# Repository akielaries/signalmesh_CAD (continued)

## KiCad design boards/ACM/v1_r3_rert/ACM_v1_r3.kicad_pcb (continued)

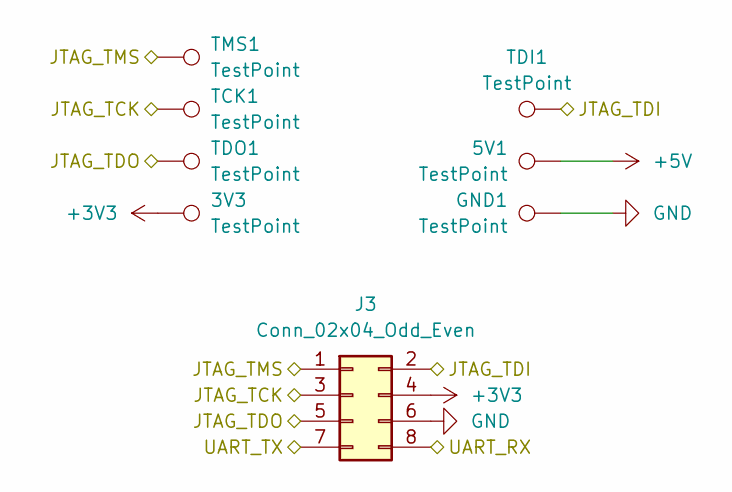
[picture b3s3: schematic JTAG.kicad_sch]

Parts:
3V3, 5V1: TestPoint; TestPoint_Pad_D1.0mm
GND1: TestPoint; TestPoint_Pad_D1.0mm
J3: Conn_02x04_Odd_Even; PinHeader_2x04_P2.54mm_Vertical_SMD
TCK1: TestPoint; TestPoint_Pad_D1.0mm
TDI1: TestPoint; TestPoint_Pad_D1.0mm
TDO1: TestPoint; TestPoint_Pad_D1.0mm
TMS1: TestPoint; TestPoint_Pad_D1.0mm

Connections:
+3V3: 3V3.1 (1_1), J3.4; also elsewhere on the board
+5V: 5V1.1 (1_1); also elsewhere on the board
/A2_JTAG_TDO: J3.5, TDO1.1 (1_1); also elsewhere on the board
/A3_JTAG_TDI: J3.2, TDI1.1 (1_1); also elsewhere on the board
/B1_JTAG_TMS: J3.1, TMS1.1 (1_1); also elsewhere on the board
/B3_IOB56A_FPGA_UART_RX: J3.7; also elsewhere on the board
/C1_JTAG_TCK: J3.3, TCK1.1 (1_1); also elsewhere on the board
/C3_IOB56B_FPGA_UART_TX: J3.8; also elsewhere on the board
GND: GND1.1 (1_1), J3.6; also elsewhere on the board

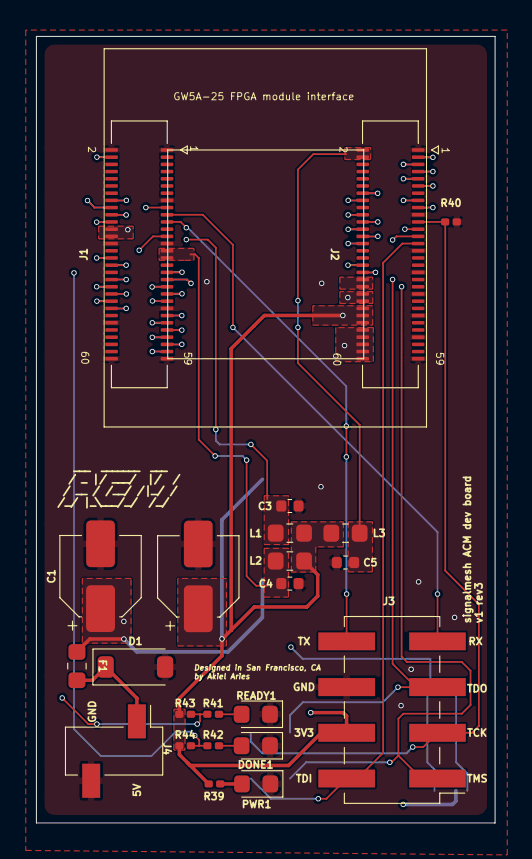
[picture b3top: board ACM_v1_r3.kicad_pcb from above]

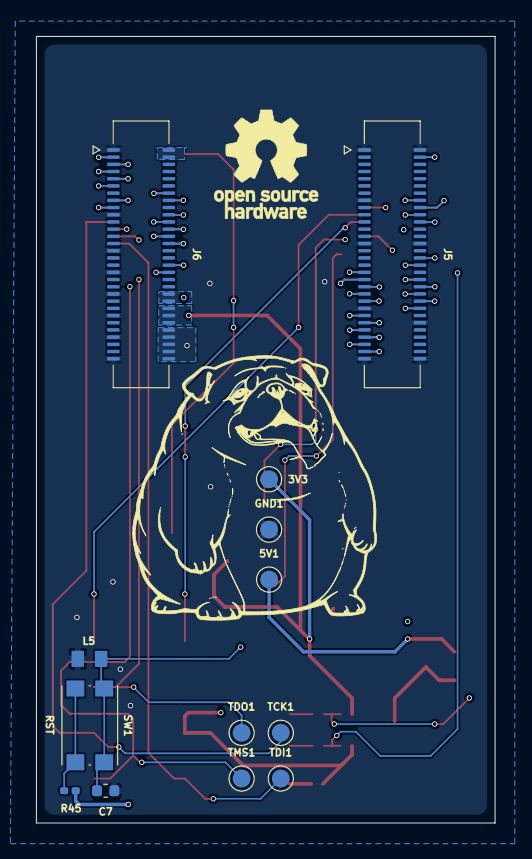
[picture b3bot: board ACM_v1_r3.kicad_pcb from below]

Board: 4 copper layers, 25.5 x 43.7 mm, 36 parts (13 on the bottom side), 66 nets.

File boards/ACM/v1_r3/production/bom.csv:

Designator,Footprint,Quantity,Value,LCSC Part #
"3V3, 5V1, GND1, TCK1, TDI1, TDO1, TMS1",TestPoint_Pad_D1.0mm,7,TestPoint,
"C1, C2",CP_Elec_4x3,2,220uF 10V,
"C3, C4, C5, C7",0402,4,100nF,
D1,D_SOD-123,1,20V 3A,
"DONE1, PWR1, READY1",0603,3,GREEN_LED,
F1,0603,1,6V 2A,
"J1, J2, J5, J6",Hirose_DF40C-60DS-0.4V_2x30_P0.4mm,4,DF40C-60DS-0.4V(51),
J3,PinHeader_2x04_P2.54mm_Vertical_SMD,1,Conn_02x04_Odd_Even,
J4,PinSocket_1x02_P2.54mm_Vertical_SMD_Pin1Left,1,Conn_01x02,
"L1, L2, L3",0603,3,PZ1608D300-3R0TF,
L5,INDC1005X45,1,LXES15AAA1-153,
"R39, R41, R42",0201,3,4.7k,
R40,0201,1,5.1K,
"R43, R44",0201,2,49.9k,
R45,0201,1,100R,
SW1,SW_Push_1P1T_NO_CK_KMR2,1,RST,

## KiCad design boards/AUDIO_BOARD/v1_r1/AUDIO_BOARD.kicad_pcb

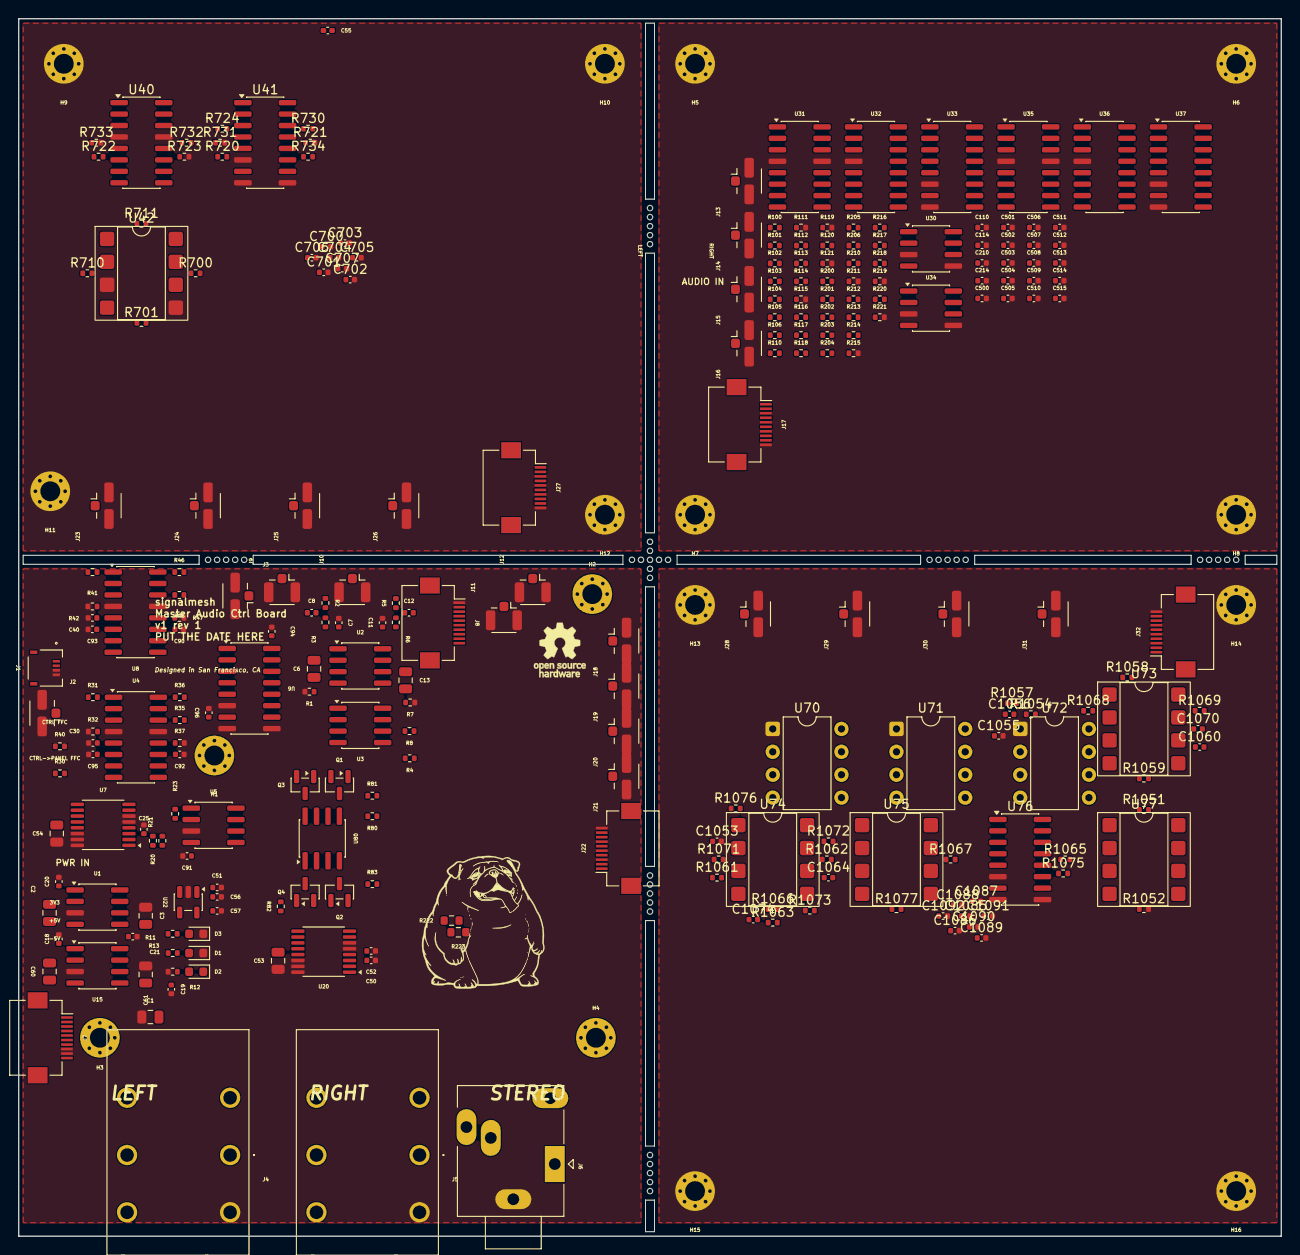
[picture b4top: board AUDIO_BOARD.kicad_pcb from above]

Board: 4 copper layers, 140.0 x 135.0 mm, 266 parts (0 on the bottom side), 170 nets, no tracks yet.

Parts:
C1, C2, C3, C53, C54: 10uF; C_0805_2012Metric
C6, C13, C60: 1uF; C_0805_2012Metric
C7, C11: 560pF; C_0402_1005Metric
C8, C12, C30, C40, C110, C114, C210, C214, C1060, C1064, C1070, C1074: 1nF; C_0402_1005Metric
C18, C19, C20, C21, C51, C52, C55, C90, C91, C92, C93, C94, C95, C96, C500, C501, C502, C503, C504, C505, C506, C507, C508, C509, C510, C511, C512, C513, C514, C515, C700, C701, C702, C703, C704, C705, C706, C707, C1085, C1086, C1087, C1088, C1089, C1090, C1091, C1092: 100nF; C_0402_1005Metric
C25, C50, C56, C57: 1uF; C_0402_1005Metric
C61: 22uF; C_0805_2012Metric
C1053: 10uF; C_0402_1005Metric
C1055, C1056: 100pF; C_0402_1005Metric
D1, D2, D3: LED; LED_0603_1608Metric
H1, H2, H3, H4, H5, H6, H7, H8, H9, H10, H11, H12, H13, H14, H15, H16: M2; MountingHole_2.2mm_M2_Pad_Via
J1: PWR FFC 4p; AMPHENOL_F3311A7H121004E200
J2: U.FL L in; U.FL_Hirose_U.FL-R-SMT-1_Vertical
J3: U.FL R in; U.FL_Hirose_U.FL-R-SMT-1_Vertical
J4: 1/4in L; ACJSMHOM
J5: 1/4in R; ACJSMHOM
J6: 3.5mm HP; Jack_3.5mm_Ledino_KB3SPRS_Horizontal
J7: CTRL FFC; Hirose_FH12-10S-0.5SH_1x10-1MP_P0.50mm_Horizontal
J8: CTRL->PANEL FFC; Hirose_FH12-10S-0.5SH_1x10-1MP_P0.50mm_Horizontal
J9: U.FL FX send L; U.FL_Hirose_U.FL-R-SMT-1_Vertical
J10: U.FL FX send R; U.FL_Hirose_U.FL-R-SMT-1_Vertical
J11: U.FL FX return L; U.FL_Hirose_U.FL-R-SMT-1_Vertical
J12: U.FL FX return R; U.FL_Hirose_U.FL-R-SMT-1_Vertical
J13: U.FL AUDIO L IN; U.FL_Hirose_U.FL-R-SMT-1_Vertical
J14: U.FL AUDIO R IN; U.FL_Hirose_U.FL-R-SMT-1_Vertical
J15: U.FL AUDIO L OUT; U.FL_Hirose_U.FL-R-SMT-1_Vertical
J16: U.FL AUDIO R OUT; U.FL_Hirose_U.FL-R-SMT-1_Vertical
J17: FILTER FFC; Hirose_FH12-10S-0.5SH_1x10-1MP_P0.50mm_Horizontal
J18: U.FL->FILT L IN; U.FL_Hirose_U.FL-R-SMT-1_Vertical
J19: U.FL->FILT R IN; U.FL_Hirose_U.FL-R-SMT-1_Vertical
J20: U.FL<-FILT L OUT; U.FL_Hirose_U.FL-R-SMT-1_Vertical
J21: U.FL<-FILT R OUT; U.FL_Hirose_U.FL-R-SMT-1_Vertical
J22: FILTER-IF FFC; Hirose_FH12-10S-0.5SH_1x10-1MP_P0.50mm_Horizontal
J23: FX-A L IN; U.FL_Hirose_U.FL-R-SMT-1_Vertical
J24: FX-A R IN; U.FL_Hirose_U.FL-R-SMT-1_Vertical
J25: FX-A L OUT; U.FL_Hirose_U.FL-R-SMT-1_Vertical
J26: FX-A R OUT; U.FL_Hirose_U.FL-R-SMT-1_Vertical
J27: FX-A CTRL; Hirose_FH12-10S-0.5SH_1x10-1MP_P0.50mm_Horizontal
J28: FX-B L IN; U.FL_Hirose_U.FL-R-SMT-1_Vertical
J29: FX-B R IN; U.FL_Hirose_U.FL-R-SMT-1_Vertical
J30: FX-B L OUT; U.FL_Hirose_U.FL-R-SMT-1_Vertical
J31: FX-B R OUT; U.FL_Hirose_U.FL-R-SMT-1_Vertical
J32: FX-B CTRL; Hirose_FH12-10S-0.5SH_1x10-1MP_P0.50mm_Horizontal
Q1, Q3: MMBT3904; SOT-23
Q2, Q4: MMBT3906; SOT-23
R1, R7, R20, R21, R23, R31, R36, R41, R46, R100, R101, R102, R103, R104, R105, R106, R112, R116, R120, R200, R201, R202, R203, R204, R205, R206, R212, R216, R220, R722, R732, R1051, R1052: 100k; R_0402_1005Metric
R2, R3, R5, R6, R113, R117, R213, R217, R724, R734, R1058, R1059, R1061, R1062, R1063, R1068, R1069, R1071, R1072, R1073: 10k; R_0402_1005Metric
R4, R8, R80, R82: 100R; R_0402_1005Metric
R11, R12, R13: 1k; R_0402_1005Metric
R30, R35, R40, R45: 20k; R_0402_1005Metric
R32, R37, R42, R47, R121, R221, R701, R711, R723, R733, R1054: 47k; R_0402_1005Metric
R81, R83: 22R; R_0402_1005Metric
R110, R114, R118, R210, R214, R218, R720, R730, R1065, R1066, R1067, R1075, R1076, R1077: 22k; R_0402_1005Metric
R111, R115, R119, R211, R215, R219, R721, R731: 220R; R_0402_1005Metric
R222, R223: 0; R_0603_1608Metric
R700, R710: 4k7; R_0402_1005Metric
R1057: 220k; R_0402_1005Metric
U1, U15: LTC660; SOIC-8_3.9x4.9mm_P1.27mm
U2, U3, U5, U30, U34, U80: OPA1678; SOIC-8_3.9x4.9mm_P1.27mm
U4, U8, U31, U32, U35, U36, U40: LM13700; SOIC-16_3.9x9.9mm_P1.27mm
U6, U41, U76: 4053; SOIC-16_3.9x9.9mm_P1.27mm
U7, U20: DAC8565; TSSOP-16_4.4x5mm_P0.65mm
U22: AP2112K-3.3; SOT-23-5
U33, U37: 4052; SOIC-16_3.9x9.9mm_P1.27mm
U42, U73, U74, U75, U77: OPA1678; DIP-8_W7.62mm_SMDSocket_SmallPads
U70, U71: MN3207; DIP-8_W7.62mm
U72: MN3101; DIP-8_W7.62mm

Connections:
+3V3: C55.1, C57.1, J8.8, R13.1, U22.5 (VOUT)
+5V: C1.1, C18.1, C20.1, C51.1, C52.1, C53.1, C54.1, C56.1, C90.1, C92.1, C94.1, J1.1, J1.2, J22.1, Q1.3 (C), Q3.3 (C), R11.1, U1.1 (BOOST), U1.8 (V+), U2.8 (V+), U3.8 (V+), U4.11 (V+), U5.8 (V+), U6.16 (VDD), U7.4 (AVDD), U7.12 (IOVDD), U7.13 (~RST), U8.11 (V+), U15.1 (BOOST), U15.8 (V+), U20.4 (AVDD), U20.12 (IOVDD), U20.13 (~RST), U22.1 (VIN), U22.3 (EN), U80.8 (V+)
-5V: C3.1, C19.1, C21.1, C61.1, C91.1, C93.1, C95.1, C96.1, D2.1 (K), J22.2, Q2.3 (C), Q4.3 (C), U1.5 (VOUT), U2.4 (V-), U3.4 (V-), U4.6 (V-), U5.4 (V-), U6.7 (VEE), U8.6 (V-), U15.5 (VOUT), U80.4 (V-)
/ANALOG_FILTER_CV/CV_CUTOFF: R20.2, U7.1 (VOUTA)
/ANALOG_FILTER_CV/CV_VCA: R36.2, R46.2, U7.7 (VOUTC)
/ANALOG_FILTER_CV/VCA_L_OUT: R37.1, U4.12, U6.13 (X1)
/ANALOG_FILTER_CV/VCA_R_OUT: R47.1, U6.1 (Y1), U8.12
/ANALOG_FILTER_CV/VCF_L_OUT: C30.1, R32.1, R35.1, U4.5
/ANALOG_FILTER_CV/VCF_R_OUT: C40.1, R42.1, R45.1, U8.5
/ANALOG_FILTER_CV/VCUTOFF: R23.2, R31.2, R41.2, U5.1
/ANALOG_FILTER_CV/VREF: C25.1, U7.3 (VREFH/VREFOUT)
/CS_DAC1: J7.4, U7.9 (~SYNC)
/CS_DAC2: J7.10, U20.9 (~SYNC)
/CS_POTS: J7.5, J8.5
/FILT_L_IN: R4.2, R30.2, U6.12 (X0)
/FILT_L_OUT: J9.1 (In), R222.2, U6.14 (X)
/FILT_R_IN: R8.2, R40.1, U6.2 (Y0)
/FILT_R_OUT: J10.1 (In), R223.2, U6.15 (Y)
/FX_CHAIN/DRV_L: R701.2, R720.1, R721.1, U41.12, U42.1
/FX_CHAIN/DRV_R: R711.2, R730.1, R731.1, U41.2, U42.7
/FX_CHAIN/TREM_L: R724.1, U40.8, U41.13
/FX_CHAIN/TREM_R: R734.1, U40.9, U41.1
/FX_CHORUS/AA_L: C1060.1, R1059.1, U70.3, U73.1
/FX_CHORUS/AA_R: C1070.1, R1069.1, U71.3, U73.7
/FX_CHORUS/BO1_L: R1061.1, U70.7
/FX_CHORUS/BO1_R: R1071.1, U71.7
/FX_CHORUS/BO2_L: R1062.1, U70.8
/FX_CHORUS/BO2_R: R1072.1, U71.8
/FX_CHORUS/CHW_L: R1067.1, U75.1, U76.13
/FX_CHORUS/CHW_R: R1077.1, U75.7, U76.1
/FX_CHORUS/CH_L_IN: R1065.1, U76.12
/FX_CHORUS/CH_R_IN: R1075.1, U76.2
/FX_CHORUS/CLK1: U70.2, U71.2, U72.2
/FX_CHORUS/CLK2: U70.6, U71.6, U72.4
/FX_CHORUS/GND: U75.3, U75.5
/FX_CHORUS/IL_L: C1060.2, R1058.2, R1059.2, U73.2
/FX_CHORUS/IL_R: C1070.2, R1068.2, R1069.2, U73.6
/FX_CHORUS/ML_L: R1065.2, R1066.2, R1067.2, U75.2
/FX_CHORUS/ML_R: R1075.2, R1076.2, R1077.2, U75.6
/FX_CHORUS/OL_L: C1064.2, R1061.2, R1062.2, R1063.2, U74.2
/FX_CHORUS/OL_R: C1074.2, R1071.2, R1072.2, R1073.2, U74.6
/FX_CHORUS/OSC1: R1054.1, R1057.2, U72.7
/FX_CHORUS/OSC2: C1056.1, R1054.2, U72.6
/FX_CHORUS/OSC3: C1055.1, C1056.2, U72.5
/FX_CHORUS/VGGB: U70.4, U71.4, U72.8
/FX_CHORUS/VMID: C1053.1, U73.3, U73.5, U74.3, U74.5, U77.1, U77.2
/FX_CHORUS/VMIDR: R1051.2, R1052.1, U77.3
/FX_CHORUS/WET_L: C1064.1, R1063.1, R1066.1, U74.1
/FX_CHORUS/WET_R: C1074.1, R1073.1, R1076.1, U74.7
/FX_CONTROL/VREF2: C50.1, U20.3 (VREFH/VREFOUT)
/FX_RET_L: J11.1 (In), J18.1 (In), R222.1
/FX_RET_R: J12.1 (In), J19.1 (In), R223.1
/GATE: J7.7, J8.9
/HP_L: J6.T, R81.2
/HP_R: J6.R, R83.2
/LINE_L: J4.T1, R80.2
/LINE_R: J5.T1, R82.2
/MASTER_FILTER/AUDIO_L_IN: J13.1 (In), R100.1
/MASTER_FILTER/AUDIO_L_OUT: J15.1 (In), U33.13 (X)
/MASTER_FILTER/AUDIO_R_IN: J14.1 (In), R200.1
/MASTER_FILTER/AUDIO_R_OUT: J16.1 (In), U37.13 (X)
/MASTER_FILTER/BPL: R113.1, R114.1, R115.1, R118.1, R119.1, U31.8, U33.14 (X1)
/MASTER_FILTER/BPR: R213.1, R214.1, R215.1, R218.1, R219.1, U35.8, U37.14 (X1)
/MASTER_FILTER/CV_CUTOFF: J17.4, R112.2, R116.2, R212.2, R216.2
/MASTER_FILTER/CV_RES: J17.6, R120.2, R220.2
/MASTER_FILTER/HPL: R103.2, R104.1, R110.1, R111.1, U30.1, U33.15 (X2)
/MASTER_FILTER/HPR: R203.2, R204.1, R210.1, R211.1, U34.1, U37.15 (X2)
/MASTER_FILTER/LPL: R101.1, R105.1, R117.1, U31.9, U33.12 (X0)
/MASTER_FILTER/LPR: R201.1, R205.1, R217.1, U35.9, U37.12 (X0)
/MASTER_FILTER/MODE_A: J17.8, U33.10 (A), U37.10 (A)
/MASTER_FILTER/MODE_B: J17.9, U33.9 (B), U37.9 (B)
/MASTER_FILTER/NOTCHL: R106.2, U30.7, U33.11 (X3)
/MASTER_FILTER/NOTCHR: R206.2, U34.7, U37.11 (X3)
/MASTER_FILTER/RESFBL: R102.1, U32.8
/MASTER_FILTER/RESFBR: R202.1, U36.8
/MF_CV_CUTOFF: J22.4, U20.1 (VOUTA)
/MF_CV_RES: J22.6, U20.2 (VOUTB)
/MF_MODE_A: J8.6, J22.8
/MF_MODE_B: J8.7, J22.9
/MODE_SEL: J7.6, U6.10 (B), U6.11 (A)
/OUTPUT_BUF/BUF_L: Q1.2 (E), Q2.2 (E), R80.1, R81.1, U80.2 (-)
/OUTPUT_BUF/BUF_R: Q3.2 (E), Q4.2 (E), R82.1, R83.1, U80.6 (-)
/SPI_MISO: J7.3, J8.4
/SPI_MOSI: J7.2, J8.3, U7.11 (DIN), U20.11 (DIN)
/SPI_SCK: J7.1, J8.2, U7.10 (SCLK), U20.10 (SCLK)
/VOL_L: J20.1 (In), U80.3 (+)
/VOL_R: J21.1 (In), U80.5 (+)
CV_MOD: R21.1, U20.7 (VOUTC)
FILT_+5V: C500.1, C502.1, C504.1, C506.1, C508.1, C510.1, C512.1, C514.1, J17.1, U30.8 (V+), U31.11 (V+), U32.11 (V+), U33.16 (VDD), U34.8 (V+), U35.11 (V+), U36.11 (V+), U37.16 (VDD)
FILT_-5V: C501.1, C503.1, C505.1, C507.1, C509.1, C511.1, C513.1, C515.1, J17.2, R113.2, R117.2, R213.2, R217.2, U30.4 (V-), U31.6 (V-), U32.6 (V-), U33.7 (VEE), U34.4 (V-), U35.6 (V-), U36.6 (V-), U37.7 (VEE)
FILT_GND: C110.2, C114.2, C210.2, C214.2, C500.2, C501.2, C502.2, C503.2, C504.2, C505.2, C506.2, C507.2, C508.2, C509.2, C510.2, C511.2, C512.2, C513.2, C514.2, C515.2, H5.1, H6.1, H7.1, H8.1, J13.2 (Ext), J14.2 (Ext), J15.2 (Ext), J16.2 (Ext), J17.3, J17.5, J17.7, J17.10, R111.2, R115.2, R119.2, R121.2, R211.2, R215.2, R219.2, R221.2, U30.3 (+), U30.5 (+), U31.4 (-), U31.13 (-), U32.4 (-), U33.6 (Inh), U33.8 (VSS), U34.3 (+), U34.5 (+), U35.4 (-), U35.13 (-), U36.4 (-), U37.6 (Inh), U37.8 (VSS)
FXA_+5V: C700.1, C702.1, C704.1, C706.1, J27.1, U40.11, U41.16, U42.8
FXA_-5V: C701.1, C703.1, C705.1, C707.1, J27.2, R724.2, R734.2, U40.6, U41.7, U42.4
FXA_CV1: J27.4, R722.2, R732.2
FXA_D1: J27.8, U41.10, U41.11
FXA_GND: C700.2, C701.2, C702.2, C703.2, C704.2, C705.2, C706.2, C707.2, H9.1, H10.1, H11.1, H12.1, J23.2 (Ext), J24.2 (Ext), J25.2 (Ext), J26.2 (Ext), J27.3, J27.5, J27.7, J27.10, R721.2, R723.2, R731.2, R733.2, U40.4, U40.13, U41.6, U41.8, U41.9, U42.3, U42.5
FXA_L_IN: J23.1 (In), R700.1
FXA_L_OUT: J25.1 (In), U41.14
FXA_R_IN: J24.1 (In), R710.1
FXA_R_OUT: J26.1 (In), U41.15
FXB_+5V: C1085.1, C1087.1, C1089.1, C1091.1, J32.1, R1051.1, U70.5, U71.5, U72.3, U73.8, U74.8, U75.8, U76.16, U77.8
FXB_-5V: C1086.1, C1088.1, C1090.1, C1092.1, J32.2, U73.4, U74.4, U75.4, U76.7, U77.4
FXB_CV1: J32.4, R1057.1
FXB_D1: J32.8, U76.11
FXB_GND: C1053.2, C1055.2, C1085.2, C1086.2, C1087.2, C1088.2, C1089.2, C1090.2, C1091.2, C1092.2, H13.1, H14.1, H15.1, H16.1, J28.2 (Ext), J29.2 (Ext), J30.2 (Ext), J31.2 (Ext), J32.3, J32.5, J32.7, J32.10, R1052.2, U70.1, U71.1, U72.1, U76.6, U76.8, U76.9
FXB_L_IN: J28.1 (In), R1058.1
FXB_L_OUT: J30.1 (In), U76.14
FXB_R_IN: J29.1 (In), R1068.1
FXB_R_OUT: J31.1 (In), U76.15
GND: C1.2, C3.2, C7.1, C11.1, C18.2, C19.2, C20.2, C21.2, C25.2, C30.2, C40.2, C50.2, C51.2, C52.2, C53.2, C54.2, C55.2, C56.2, C57.2, C61.2, C90.2, C91.2, C92.2, C93.2, C94.2, C95.2, C96.2, D1.1 (K), D3.1 (K), J1.3, J1.4, J2.2 (Ext), J3.2 (Ext), J4.S1, J5.S1, J6.S, J7.8, J7.9, J8.1, J9.2 (Ext), J10.2 (Ext), J11.2 (Ext), J12.2 (Ext), J18.2 (Ext), J19.2 (Ext), J20.2 (Ext), J21.2 (Ext), J22.3, J22.5, J22.7, J22.10, R1.2, R7.2, R12.1, R32.2, R37.2, R42.2, R47.2, U1.3 (GND), U4.4 (-), U4.13 (-), U5.3 (+), U6.6 (Inh), U6.8 (VSS), U6.9 (C), U7.5 (VREFL), U7.6 (GND), U7.14 (RSTSEL), U7.15 (~ENABLE), U7.16 (LDAC), U8.4 (-), U8.13 (-), U15.3 (GND), U20.5 (VREFL), U20.6 (GND), U20.14 (RSTSEL), U20.15 (~ENABLE), U20.16 (LDAC), U22.2 (GND)
unnamed: C8.1, R2.2, R3.1
unnamed: C12.1, R5.2, R6.1
unnamed: C110.1, U31.5, U31.7
unnamed: C114.1, U31.10, U31.12
unnamed: C210.1, U35.5, U35.7
unnamed: C214.1, U35.10, U35.12
unnamed: D1.2 (A), R11.2
unnamed: D2.2 (A), R12.2
unnamed: D3.2 (A), R13.2
unnamed: J2.1 (In), R2.1
unnamed: J3.1 (In), R5.1
unnamed: Q1.1 (B), Q2.1 (B), U80.1
unnamed: Q3.1 (B), Q4.1 (B), U80.7
unnamed: R31.1, U4.1
unnamed: R36.1, U4.16
unnamed: R41.1, U8.1
unnamed: R46.1, U8.16
unnamed: R112.1, U31.1
unnamed: R116.1, U31.16
unnamed: R120.1, U32.1
unnamed: R121.1, U32.5, U32.7
unnamed: R212.1, U35.1
unnamed: R216.1, U35.16
unnamed: R220.1, U36.1
unnamed: R221.1, U36.5, U36.7
unnamed: R722.1, U40.1
unnamed: R723.1, U40.5, U40.7
unnamed: R732.1, U40.16
unnamed: R733.1, U40.10, U40.12
unnamed: C2.1, U1.2 (CAP+)
unnamed: C2.2, U1.4 (CAP-)
unnamed: C7.2, R3.2, U2.3 (+)
unnamed: C6.1, C8.2, U2.1, U2.2 (-)
unnamed: C11.2, R6.2, U2.5 (+)
unnamed: C12.2, C13.1, U2.6 (-), U2.7
unnamed: C6.2, R1.1, U3.3 (+)
unnamed: R4.1, U3.1, U3.2 (-)
unnamed: C13.2, R7.1, U3.5 (+)
unnamed: R8.1, U3.6 (-), U3.7
unnamed: R35.2, U4.14 (+)
unnamed: R30.1, U4.3 (+)
unnamed: R20.1, R21.2, R23.1, U5.2 (-)
unnamed: R45.2, U8.14 (+)
unnamed: R40.2, U8.3 (+)
unnamed: C60.1, U15.2 (CAP+)
unnamed: C60.2, U15.4 (CAP-)
unnamed: R100.2, R101.2, R102.2, R103.1, U30.2 (-)
unnamed: R104.2, R105.2, R106.1, U30.6 (-)
unnamed: R114.2, U31.14 (+)
unnamed: R110.2, U31.3 (+)
unnamed: R118.2, U32.3 (+)
unnamed: R200.2, R201.2, R202.2, R203.1, U34.2 (-)
unnamed: R204.2, R205.2, R206.1, U34.6 (-)
unnamed: R214.2, U35.14 (+)
unnamed: R210.2, U35.3 (+)
unnamed: R218.2, U36.3 (+)
unnamed: R730.2, U40.14
unnamed: R720.2, U40.3
unnamed: R700.2, R701.1, U42.2
unnamed: R710.2, R711.1, U42.6

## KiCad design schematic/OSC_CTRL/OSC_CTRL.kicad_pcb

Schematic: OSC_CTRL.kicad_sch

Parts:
C2: 220uF 10V; CP_Elec_4x3
C3, C4: 100nF; C_0402_1005Metric
D1: 20V 3A; D_SOD-123
F2: 4V 2A; Fuse_0603_1608Metric
H1, H2, H3, H4: M2; MountingHole_2.2mm_M2_Pad_Via
J5: OSC_CTRL; GCT_FFC2B28-20-G; PARTREV A
PWR1: GREEN_LED; LED_0603_1608Metric
R39: 4.7k; R_0201_0603Metric; DigiKey_Part_Number 311-10.0KCRCT-ND
R40, R41, R42: 10K; R_0201_0603Metric; DigiKey_Part_Number 311-10.0KCRCT-ND
RV6, RV7, RV8, RV9, RV11, RV12, RV13, RV14, RV16, RV17, RV18, RV19: 10K; Potentiometer_Bourns_PTA4543_Single_Slide
RV10, RV15, RV20: 10K; Potentiometer_Piher_PC-16_Single_Horizontal
S1, S2, S3: SRBM149501; SW_SRBM149501; PARTREV N/A
TP1: 1v1; TestPoint_Pad_D1.0mm
TP2: 2v2; TestPoint_Pad_D1.0mm
TP3: FPC_3V3_TP; TestPoint_Pad_D1.0mm
TP4: FPC_GND_TP; TestPoint_Pad_D1.0mm
U3, U4: CD74HC4067SM; SSOP-24_5.3x8.2mm_P0.65mm

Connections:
3V3: C2.1, C3.2, C4.2, F2.1, R39.2, R40.2, RV6.1, RV7.1, RV8.1, RV9.1, RV10.1, RV11.1, RV12.1, RV13.1, RV14.1, RV15.1, RV16.1, RV17.1, RV18.1, RV19.1, RV20.1, S1.5F, S2.5F, S3.5F, U3.24 (VCC), U4.24 (VCC)
3V3_IN: D1.1 (K), F2.2, J5.9, J5.19, TP3.1 (1_1)
/NODE_A: R40.1, R41.2, S1.4F, S2.4F, S3.4F, TP2.1 (1_1)
/NODE_B: R41.1, R42.2, S1.3F, S2.3F, S3.3F, TP1.1 (1_1)
/OSC_1_ATK: RV11.2, U3.9 (I0)
/OSC_1_DEC: RV12.2, U3.8 (I1)
/OSC_1_REL: RV14.2, U3.6 (I3)
/OSC_1_SUS: RV13.2, U3.7 (I2)
/OSC_1_VOL: RV15.2, U3.5 (I4)
/OSC_1_WAVE: S1.1F, U4.9 (I0)
/OSC_2_ATK: RV6.2, U3.4 (I5)
/OSC_2_DEC: RV7.2, U3.3 (I6)
/OSC_2_REL: RV9.2, U3.23 (I8)
/OSC_2_SUS: RV8.2, U3.2 (I7)
/OSC_2_VOL: RV10.2, U3.22 (I9)
/OSC_2_WAVE: S2.1F, U4.8 (I1)
/OSC_3_ATK: RV16.2, U3.21 (I10)
/OSC_3_DEC: RV17.2, U3.20 (I11)
/OSC_3_REL: RV19.2, U3.18 (I13)
/OSC_3_SUS: RV18.2, U3.19 (I12)
/OSC_3_VOL: RV20.2, U3.17 (I14)
/OSC_3_WAVE: S3.1F, U4.7 (I2)
/SEL_A_BIT_0: J5.2, U3.10 (S0)
/SEL_A_BIT_1: J5.3, U3.11 (S1)
/SEL_A_BIT_2: J5.4, U3.14 (S2)
/SEL_A_BIT_3: J5.5, U3.13 (S3)
/SEL_B_BIT_0: J5.12, U4.10 (S0)
/SEL_B_BIT_1: J5.13, U4.11 (S1)
/SEL_B_BIT_2: J5.14, U4.14 (S2)
/SEL_B_BIT_3: J5.15, U4.13 (S3)
/STM32_ADC_1_10: J5.7, U3.1 (COM)
/STM32_ADC_3_1: J5.17, U4.1 (COM)
GND: C2.2, C3.1, C4.1, D1.2 (A), J5.1, J5.6, J5.8, J5.10, J5.11, J5.16, J5.18, J5.20, J5.S1 (SHIELD), J5.S2 (SHIELD), PWR1.1 (K), R42.1, RV6.3, RV7.3, RV8.3, RV9.3, RV10.3, RV11.3, RV12.3, RV13.3, RV14.3, RV15.3, RV16.3, RV17.3, RV18.3, RV19.3, RV20.3, S1.2F, S2.2F, S3.2F, TP4.1 (1_1), U3.12 (GND), U3.15 (~E), U4.12 (GND), U4.15 (~E)
unnamed: PWR1.2 (A), R39.1

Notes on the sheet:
2.2v
Board power supply
1.1v
ASDR
VOLUME
Oscillator Control Board
WAVEFORM SELECT
OSCILLATOR 2
POWER
OSCILLATOR 3
Each pad is capable of supplying 0.5A
Board power input
MOUNTS
WAVE_SEL
LEDs
PWR
OSCILLATOR 1

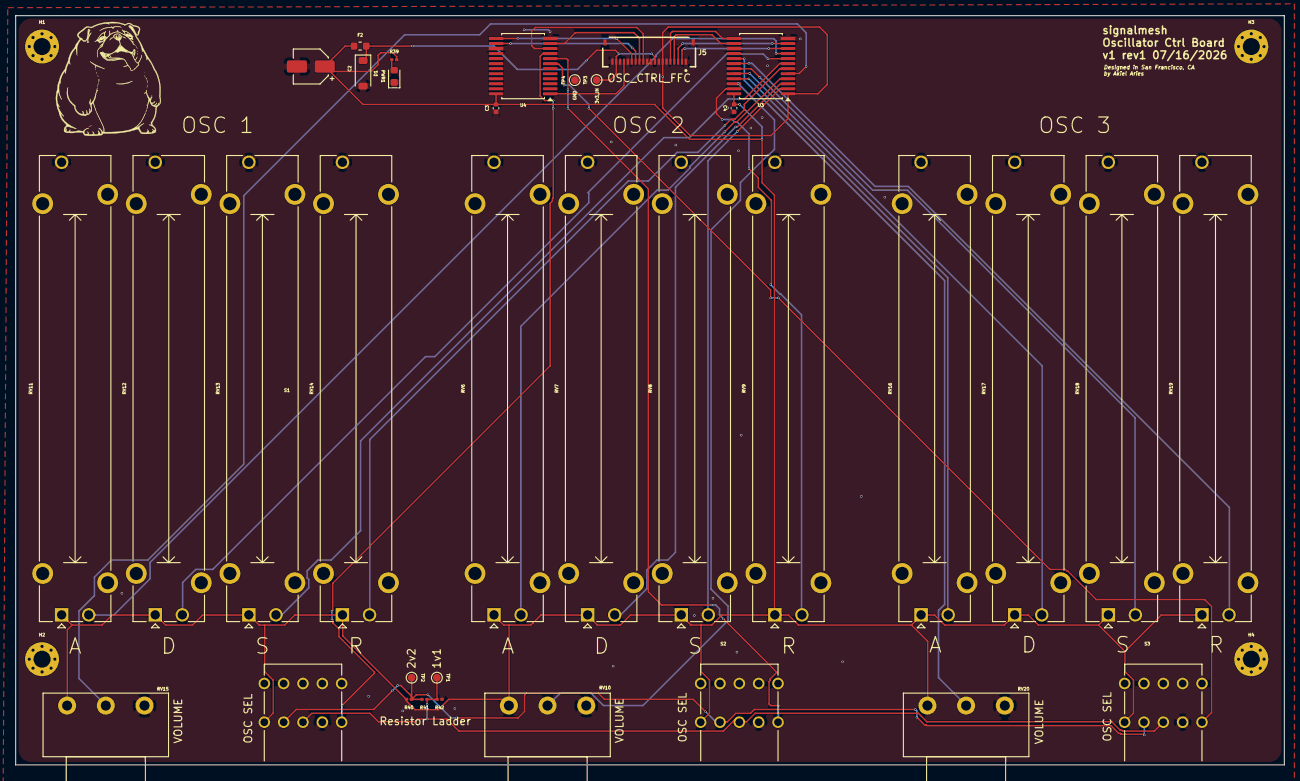
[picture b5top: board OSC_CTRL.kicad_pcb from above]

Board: 2 copper layers, 164.0 x 96.8 mm, 39 parts (0 on the bottom side), 34 nets.

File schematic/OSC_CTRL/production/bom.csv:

Designator,Footprint,Quantity,Value,LCSC Part #
C2,CP_Elec_4x3,1,220uF 10V,
"C3, C4",0402,2,100nF,
D1,D_SOD-123,1,20V 3A,
F2,0603,1,4V 2A,
"H1, H2, H3, H4",MountingHole_2.2mm_M2_Pad_Via,4,M2,
J5,GCT_FFC2B28-20-G,1,OSC_CTRL,
PWR1,0603,1,GREEN_LED,
R39,0201,1,4.7k,
"R40, R41, R42",0201,3,10K,
"RV10, RV15, RV20",Potentiometer_Piher_PC-16_Single_Horizontal,3,10K,
"RV11, RV12, RV13, RV14, RV16, RV17, RV18, RV19, RV6, RV7, RV8, RV9",Potentiometer_Bourns_PTA4543_Single_Slide,12,10K,
"S1, S2, S3",SW_SRBM149501,3,SRBM149501,
TP1,TestPoint_Pad_D1.0mm,1,1v1,
TP2,TestPoint_Pad_D1.0mm,1,2v2,
TP3,TestPoint_Pad_D1.0mm,1,FPC_3V3_TP,
TP4,TestPoint_Pad_D1.0mm,1,FPC_GND_TP,
"U3, U4",SSOP-24_5.3x8.2mm_P0.65mm,2,CD74HC4067SM,

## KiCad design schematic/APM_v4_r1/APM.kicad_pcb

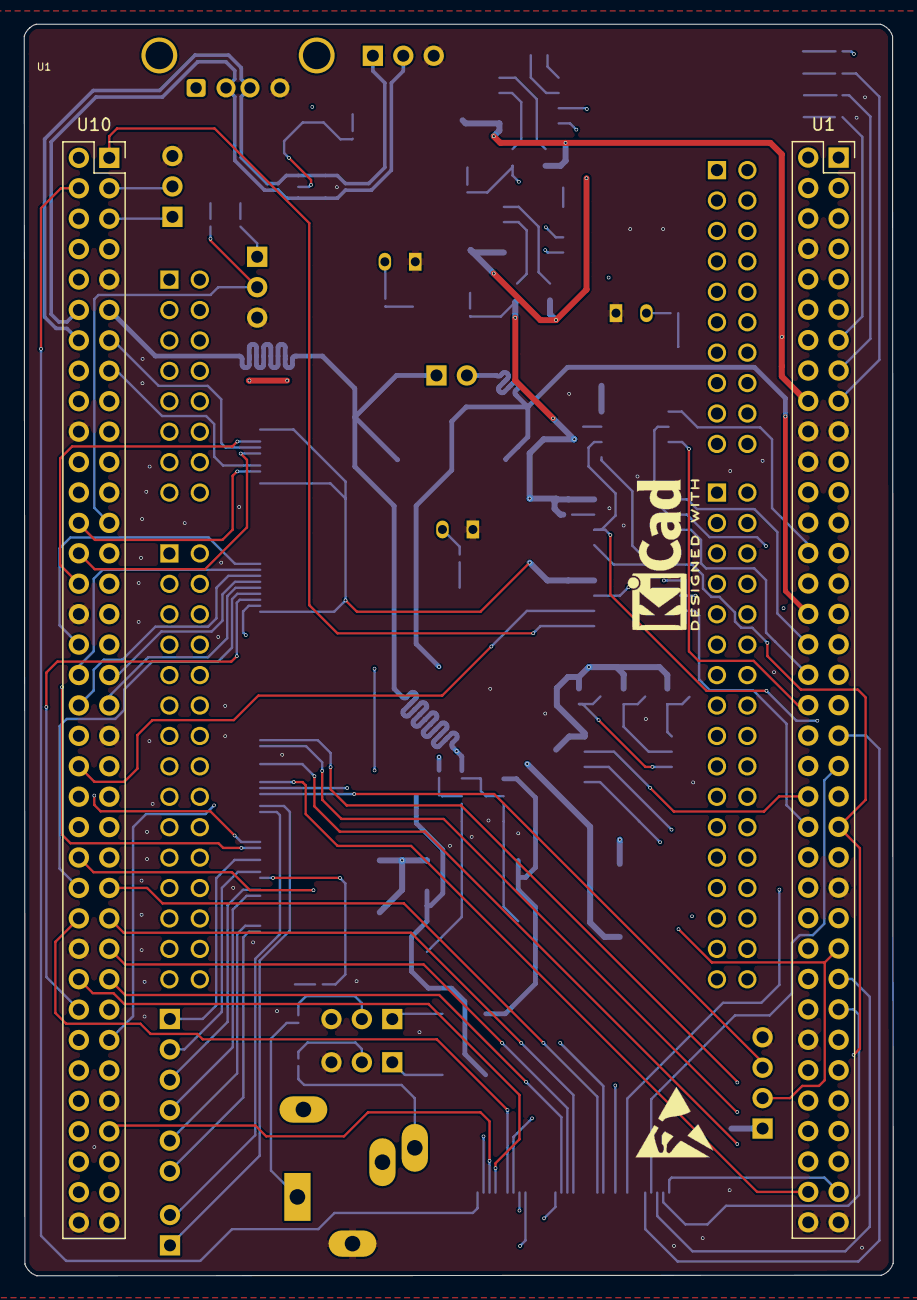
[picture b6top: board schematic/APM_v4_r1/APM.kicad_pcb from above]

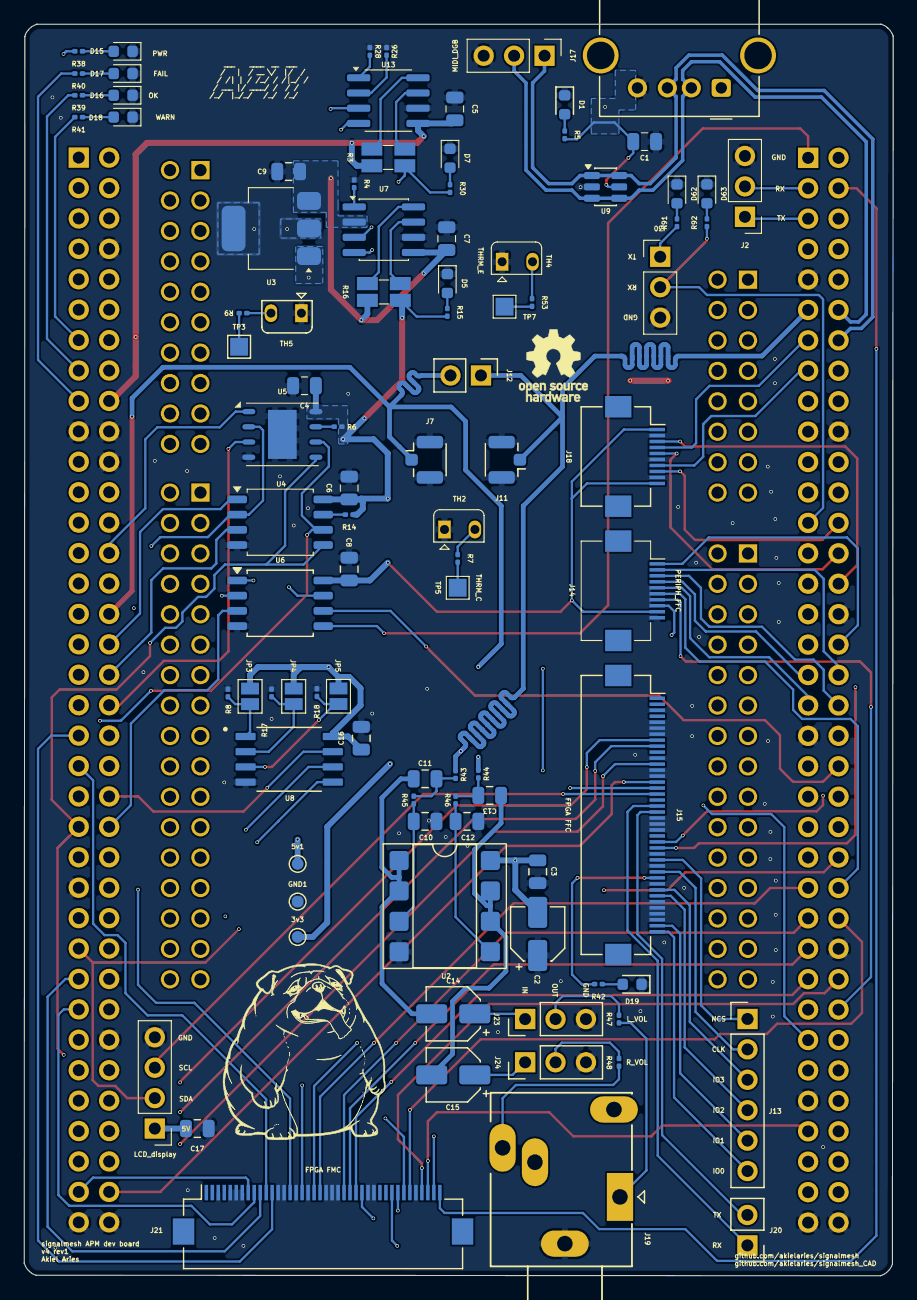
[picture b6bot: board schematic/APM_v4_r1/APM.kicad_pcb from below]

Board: 4 copper layers, 72.5 x 104.5 mm, 97 parts (94 on the bottom side), 119 nets.

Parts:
3v3: 3v3; TestPoint_Pad_D1.0mm
5v1: 5v; TestPoint_Pad_D1.0mm
C1: 22pf; C_0805_2012Metric
C2, C14, C15: 10uF; CP_Elec_4x3
C3, C4, C6, C8, C9, C16, C17: 100nF; C_0805_2012Metric
C5, C7: 0.1uf; C_0805_2012Metric
C10, C12: 2.2nF; C_0805_2012Metric
C11, C13: 4.7nF; C_0805_2012Metric
D1, D5, D7: LED_PWR; LED_0603_1608Metric
D15: PWR; LED_0603_1608Metric
D16: OK; LED_0603_1608Metric
D17: FAIL; LED_0603_1608Metric
D18: WARN; LED_0603_1608Metric
D19: FPGA_PWR; LED_0603_1608Metric
D62: TXD; LED_0603_1608Metric
D63: RXD; LED_0603_1608Metric
GND1: GND; TestPoint_Pad_D1.0mm
J2: CAN; PinHeader_1x03_P2.54mm_Vertical
J4: LCD_display; PinHeader_1x04_P2.54mm_Vertical
J7: DAC_R_PRB; U.FL_Hirose_U.FL-R-SMT-1_Vertical
J11: DAC_L_PRB; U.FL_Hirose_U.FL-R-SMT-1_Vertical
J12: Conn_01x02; PinHeader_1x02_P2.54mm_Vertical
J13: Conn_01x06; PinHeader_1x06_P2.54mm_Vertical
J14: POT_FFC; Hirose_FH12-10S-0.5SH_1x10-1MP_P0.50mm_Horizontal
J15: FPGA FFC; Hirose_FH12-40S-0.5SH_1x40-1MP_P0.50mm_Horizontal
J16: USB_A_FEMALE; USB_A_Molex_67643_Horizontal
J17: MIDI_DGB; PinHeader_1x03_P2.54mm_Vertical
J18: CTRL_FFC; Hirose_FH12-10S-0.5SH_1x10-1MP_P0.50mm_Horizontal
J19: AudioPlug3; Jack_3.5mm_Ledino_KB3SPRS_Horizontal
J20: FPGA_UART; PinHeader_1x02_P2.54mm_Vertical
J21: FPGA FMC; Hirose_FH12-40S-0.5SH_1x40-1MP_P0.50mm_Horizontal
J23: VOL_L_CTRL; PinHeader_1x03_P2.54mm_Vertical
J24: VOL_R_CTRL; PinHeader_1x03_P2.54mm_Vertical
J30: UART_DEBUG; PinHeader_1x03_P2.54mm_Vertical
JP3: A0; SolderJumper-2_P1.3mm_Open_Pad1.0x1.5mm
JP4: A1; SolderJumper-2_P1.3mm_Open_Pad1.0x1.5mm
JP5: A2; SolderJumper-2_P1.3mm_Open_Pad1.0x1.5mm
R3, R16: 0.1; R_Shunt_Ohmite_LVK12
R4, R6, R7, R8, R9, R14, R17, R18, R26, R28, R53: 10k; R_0201_0603Metric
R5, R15, R30, R39, R40, R41, R42, R91, R92: 300; R_0201_0603Metric
R38: 1.2k; R_0201_0603Metric
R43, R44, R45, R46: 2.4k; R_0201_0603Metric
R47, R48: 47; R_0201_0603Metric
TH2, TH4, TH5: 10k; Heraeus_TO-92-2
TP3: THRM_A; TestPoint_Pad_1.5x1.5mm
TP5: THRM_C; TestPoint_Pad_1.5x1.5mm
TP7: THRM_E; TestPoint_Pad_1.5x1.5mm
U1: NUCLEO-H753ZI; ST_Morpho_and_Zio_Connectors_144_STLink
U1#2, U10: PinSocket_2x36_P2.54mm_Vertical
U2: OPA1678; DIP-8_W7.62mm_SMDSocket_SmallPads
U3: LT1963AxST-3.3; SOT-223-3_TabPin2
U4, U6: W25Q128JVS; SOIC-8_5.3x5.3mm_P1.27mm
U5: MR25H40; DFN-S-8-1EP_6x5mm_P1.27mm
U7, U13: INA219AxD; SOIC-8_3.9x4.9mm_P1.27mm
U8: 24LC1025-I_P; SOIC127P794X202-8N
U9: USBLC6-2SC6; SOT-23-6

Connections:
3V3_APM: 3v3.1 (1_1), C4.1, C6.1, C8.1, C16.1, J14.9, J18.1, J18.10, JP3.2 (B), JP4.2 (B), JP5.2 (B), R6.1, R14.1, R15.2, R16.4, U4.8 (VCC), U5.8 (VDD), U6.8 (VCC), U8.8 (VCC)
3V3_LDO: C7.2, C9.1, R16.1, U3.3 (OUT), U7.2 (A0), U7.5 (VS)
5V_APM: C1.2, C2.2, C3.2, C17.2, J4.1, J16.1 (VBUS), R3.4, R5.2, R30.2, R38.2, U2.8 (V+), U3.1 (IN), U9.5 (VBUS)
5V_APM_MCU: 5v1.1 (1_1), C5.2, R3.1, U1#2.18 (5V), U13.5 (VS)
/ADC_POT_1: J14.1, U10.34 (PC4)
/ADC_POT_2: J14.2, U10.36 (PF5)
/ADC_POT_3: J14.3, U10.38 (PF4)
/ADC_POT_4: J14.4, U10.35 (PA2)
/ADC_POT_5: J14.5, U10.37 (PA3)
/ADC_POT_6: J14.6, U10.50 (PF14)
/ADC_POT_7: J14.7, U10.58 (PF3)
/ADC_POT_8: J14.8, U10.59 (PF12)
/APM_CAN_RD: J2.2, U10.3 (PB8)
/APM_CAN_TD: J2.1, U10.5 (PB9)
/APM_DBG_RX: J30.2, R92.1, U10.25 (PB10)
/APM_DBG_TX: J30.1, R91.1, U10.21 (PA9)
/APM_EEPROM_EN: U1#2.44 (PG3), U8.7 (WP)
/APM_FMC_DA0: J21.33, U10.46 (PD14)
/APM_FMC_DA1: J21.34, U10.48 (PD15)
/APM_FMC_DA2: J21.9, U1#2.57 (PD0)
/APM_FMC_DA3: J21.10, U1#2.55 (PD1)
/APM_FMC_DA4: J21.32, U10.44 (PE7)
/APM_FMC_DA5: J21.27, U10.40 (PE8)
/APM_FMC_DA6: J21.35, U10.52 (PE9)
/APM_FMC_DA7: J21.19, U10.47 (PE10)
/APM_FMC_DA8: J21.37, U10.56 (PE11)
/APM_FMC_DA9: J21.20, U10.49 (PE12)
/APM_FMC_DA10: J21.26, U10.55 (PE13)
/APM_FMC_DA11: J21.24, U10.51 (PE14)
/APM_FMC_DA12: J21.25, U10.53 (PE15)
/APM_FMC_DA13: J21.39, U10.10 (PD8)
/APM_FMC_DA14: J21.8, U1#2.69 (PD9)
/APM_FMC_DA15: J21.38, U10.65 (PD10)
/APM_FMC_NE1: J21.17, U10.19 (PC7)
/APM_FMC_NL: J21.15, U1#2.21 (PB7)
/APM_FMC_NOE: J21.12, U1#2.39 (PD4)
/APM_FMC_NWAIT: J21.40, U10.4 (PC6)
/APM_FMC_NWE: J21.11, U1#2.41 (PD5)
/APM_FPGA_UART_RX: J15.25, U10.23 (PA8)
/APM_FPGA_UART_TX: J15.26, U10.31 (PB3)
/APM_I2C2_SCL: J4.3, J15.17, U1#2.51 (PF1), U7.4 (SCL), U8.6 (SCL), U13.4 (SCL)
/APM_I2C2_SDA: J4.2, J15.16, U1#2.53 (PF0), U7.3 (SDA), U8.5 (SDA), U13.3 (SDA)
/APM_LED_FAIL: R41.2, U1#2.13 (PA13)
/APM_LED_OK: R39.2, U1#2.15 (PA14)
/APM_LED_WARN: R40.2, U1#2.17 (PA15)
/APM_MRAM_EN: U1#2.38 (PC0), U5.3 (~WP)
/APM_SPI1_CS: J15.12, U1#2.66 (PG10)
/APM_SPI1_MISO: J15.9, U1#2.63 (PG9), U4.2 (DO/IO_{1}), U5.2 (SO)
/APM_SPI1_MOSI: J15.8, U1#2.45 (PD7), U4.5 (DI/IO_{0}), U5.5 (SI)
/APM_SPI1_SCK: J15.15, U1#2.70 (PG11), U4.6 (CLK), U5.6 (SCK)
/APM_SPI2_MISO: J18.5, U10.28 (PB14)
/APM_SPI2_MOSI: J18.8, U10.26 (PB15)
/APM_SPI2_SCK: J18.3, U10.30 (PB13)
/APM_SPIFLASH_EN: U1#2.36 (PC1), U4.3 (~WP/IO_{2})
/AUDIO_APM/OUT_L: J23.2, R47.2
/AUDIO_APM/OUT_R: J24.2, R48.2
/AUDIO_APM/VOL_L_IN: C14.1, J23.1
/AUDIO_APM/VOL_R_IN: C15.1, J24.1
/DAC_1-1_R: J7.1 (In), J12.2, R44.1, U1#2.32 (PA4)
/DAC_1-2_L: J11.1 (In), J12.1, R43.1, U10.11 (PA5)
/FPGA_UART_RX: J15.20, J20.2
/FPGA_UART_TX: J15.19, J20.1
/MIDI_FS_D+: J16.3 (D+), J17.1, U9.1 (I/O1), U9.6 (I/O1), U10.14 (PA11)
/MIDI_FS_D-: J16.2 (D-), J17.2, U9.3 (I/O2), U9.4 (I/O2), U10.12 (PA12)
/NC: U1#2.25 (PC14), U1#2.27 (PC15), U1#2.29 (PH0)
/QSPI1_D0: U6.5 (DI/IO_{0}), U10.1 (PC9)
/QSPI1_D1: U1#2.1 (PC10), U6.2 (DO/IO_{1})
/QSPI1_D2: U1#2.46 (PE2), U6.3 (~WP/IO_{2})
/QSPI1_D3: U1#2.30 (PA1), U6.7 (~HOLD/~RESET/IO_{3})
/QSPI1_NCS: U6.1 (~CS), U10.70 (PG6)
/QSPI_CLK: J13.2, J15.30
/QSPI_IO_0: J13.6, J15.40
/QSPI_IO_1: J13.5, J15.39
/QSPI_IO_2: J13.4, J15.34
/QSPI_IO_3: J13.3, J15.33
/QSPI_NCS: J13.1, J15.28
/QSPI_SCK2: U6.6 (CLK), U10.42 (PF10)
/SPIFLASH_CS: U1#2.34 (PB0), U4.1 (~CS)
/SPIMRAM_CS: U1#2.28 (PA0), U5.1 (~CS)
/SR_GPIO1: J18.4, U10.13 (PA6)
/SR_GPIO2: J18.7, U10.15 (PA7)
/THRM_A: R9.2, TP3.1 (1_1)
/THRM_C: R7.2, TP5.1 (1_1)
/THRM_E: R53.2, TP7.1 (1_1)
DAC_L_OUT: C11.1, C14.2, U2.1, U2.2 (-)
DAC_R_OUT: C13.1, C15.2, U2.6 (-), U2.7
FPGA_3V3_OUT1: J15.31, R42.2
GND: C1.1, C2.1, C3.1, C4.2, C5.1, C6.2, C7.1, C8.2, C9.2, C10.1, C12.1, C16.2, C17.1, D1.1 (K), D5.1 (K), D7.1 (K), D15.1 (K), D16.1 (K), D17.1 (K), D18.1 (K), D19.1 (K), D62.1 (K), D63.1 (K), GND1.1 (1_1), J2.3, J4.4, J7.2 (Ext), J11.2 (Ext), J14.10, J15.3, J15.5, J15.6, J15.7, J15.11, J15.13, J15.14, J15.21, J15.22, J15.23, J15.27, J15.29, J15.32, J15.35, J15.36, J15.37, J15.38, J16.4 (GND), J17.3, J18.2, J18.6, J18.9, J19.S, J21.3, J21.5, J21.6, J21.7, J21.13, J21.14, J21.16, J21.18, J21.21, J21.22, J21.23, J21.28, J21.29, J21.36, J23.3, J24.3, J30.3, R4.1, R8.2, R17.2, R18.2, R26.1, R28.1, TH2.1, TH4.1, TH5.1, U1#2.8 (GND_CN11), U1#2.19 (GND_CN11), U1#2.20 (GND_CN11), U1#2.22 (GND_CN11), U1#2.49 (GND_CN11), U1#2.60 (GND_CN11), U1#2.71 (GND_CN11), U1#2.72 (GND_CN11), U2.4 (V-), U3.2 (GND), U4.4 (GND), U5.4 (VSS), U5.9 (PAD), U6.4 (GND), U7.6 (GND), U8.4 (VSS), U9.2 (GND), U10.9 (GND_CN12), U10.20 (GND_CN12), U10.32 (AGND_CN12), U10.39 (GND_CN12), U10.54 (GND_CN12), U10.63 (GND_CN12), U10.71 (GND_CN12), U10.72 (GND_CN12), U13.6 (GND)
unnamed: C11.2, R43.2, R45.1
unnamed: C13.2, R44.2, R46.1
unnamed: D1.2 (A), R5.1
unnamed: D5.2 (A), R15.1
unnamed: D7.2 (A), R30.1
unnamed: D15.2 (A), R38.1
unnamed: D16.2 (A), R39.1
unnamed: D17.2 (A), R40.1
unnamed: D18.2 (A), R41.1
unnamed: D19.2 (A), R42.1
unnamed: D62.2 (A), R91.2
unnamed: D63.2 (A), R92.2
unnamed: J19.R, R48.1
unnamed: J19.T, R47.1
unnamed: JP3.1 (A), R8.1, U8.1 (A0)
unnamed: JP4.1 (A), R17.1, U8.2 (A1)
unnamed: JP5.1 (A), R18.1, U8.3 (A2)
unnamed: R7.1, TH2.2
unnamed: R9.1, TH5.2
unnamed: R53.1, TH4.2
unnamed: C10.2, R45.2, U2.3 (+)
unnamed: C12.2, R46.2, U2.5 (+)
unnamed: R14.2, U4.7 (~HOLD/~RESET/IO_{3})
unnamed: R6.2, U5.7 (~HOLD)
unnamed: R4.2, U7.1 (A1)
unnamed: R16.2, U7.8 (IN+)
unnamed: R16.3, U7.7 (IN-)
unnamed: R26.2, U13.2 (A0)
unnamed: R28.2, U13.1 (A1)
unnamed: R3.2, U13.8 (IN+)
unnamed: R3.3, U13.7 (IN-)

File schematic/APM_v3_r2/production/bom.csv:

Designator,Footprint,Quantity,Value,LCSC Part #
C1,0805,1,22pf,
"C4, C6, C8",0805,3,100nF,
"C5, C7",0805,2,0.1uf,
"D1, D5, D7",0603,3,LED_PWR,
D15,0603,1,PWR,
D16,0603,1,OK,
D17,0603,1,FAIL,
D18,0603,1,WARN,
D19,0603,1,FPGA_PWR,
D62,0603,1,TXD,
D63,0603,1,RXD,
J1,PinHeader_1x03_P2.54mm_Vertical,1,ACM_CTRL,
J11,U.FL_Hirose_U.FL-R-SMT-1_Vertical,1,DAC_L_PRB,
J12,PinHeader_1x02_P2.54mm_Vertical,1,Conn_01x02,
J13,PinHeader_1x06_P2.54mm_Vertical,1,Conn_01x06,
J14,Hirose_FH12-10S-0.5SH_1x10-1MP_P0.50mm_Horizontal,1,PERIPH_FFC,
J15,Hirose_FH12-40S-0.5SH_1x40-1MP_P0.50mm_Horizontal,1,FPGA FFC,
J16,USB_A_Molex_67643_Horizontal,1,USB_A_FEMALE,
J17,PinHeader_1x03_P2.54mm_Vertical,1,MIDI_DGB,
J2,PinHeader_1x03_P2.54mm_Vertical,1,CAN,
J20,PinHeader_1x02_P2.54mm_Vertical,1,FPGA_UART,
J21,PinHeader_1x02_P2.54mm_Vertical,1,APM_FPGA_UART,
J3,PinHeader_1x03_P2.54mm_Vertical,1,7SDD_CTRL,
J30,PinHeader_1x03_P2.54mm_Vertical,1,UART_DEBUG,
J4,PinHeader_1x04_P2.54mm_Vertical,1,LCD_display,
J5,PinHeader_1x02_P2.54mm_Vertical,1,INTRPT,
J7,U.FL_Hirose_U.FL-R-SMT-1_Vertical,1,DAC_R_PRB,
"R14, R17, R18, R26, R28, R4, R53, R6, R7, R8, R9",0201,11,10k,
"R15, R30, R39, R40, R41, R42, R5, R91, R92",0201,9,300,
"R16, R3",R_Shunt_Ohmite_LVK12,2,0.1,
R38,0201,1,1.2k,
"TH2, TH4, TH5",Heraeus_TO-92-2,3,10k,
TP3,TestPoint_Pad_1.5x1.5mm,1,THRM_A,
TP5,TestPoint_Pad_1.5x1.5mm,1,THRM_C,
TP7,TestPoint_Pad_1.5x1.5mm,1,THRM_E,
U1_2,ST_Morpho_and_Zio_Connectors_144_STLink,1,NUCLEO-H753ZI,
"U1, U10",PinSocket_2x36_P2.54mm_Vertical,2,~,
"U13, U7",SOIC-8_3.9x4.9mm_P1.27mm,2,INA219AxD,
U3,SOT-223-3_TabPin2,1,LT1963AxST-3.3,
"U4, U6",SOIC-8_5.3x5.3mm_P1.27mm,2,W25Q128JVS,
U5,DFN-S-8-1EP_6x5mm_P1.27mm,1,MR25H40,
U8,DIP787W46P254L927H533Q8,1,24LC1025-I_P,
U9,SOT-23-6,1,USBLC6-2SC6,
